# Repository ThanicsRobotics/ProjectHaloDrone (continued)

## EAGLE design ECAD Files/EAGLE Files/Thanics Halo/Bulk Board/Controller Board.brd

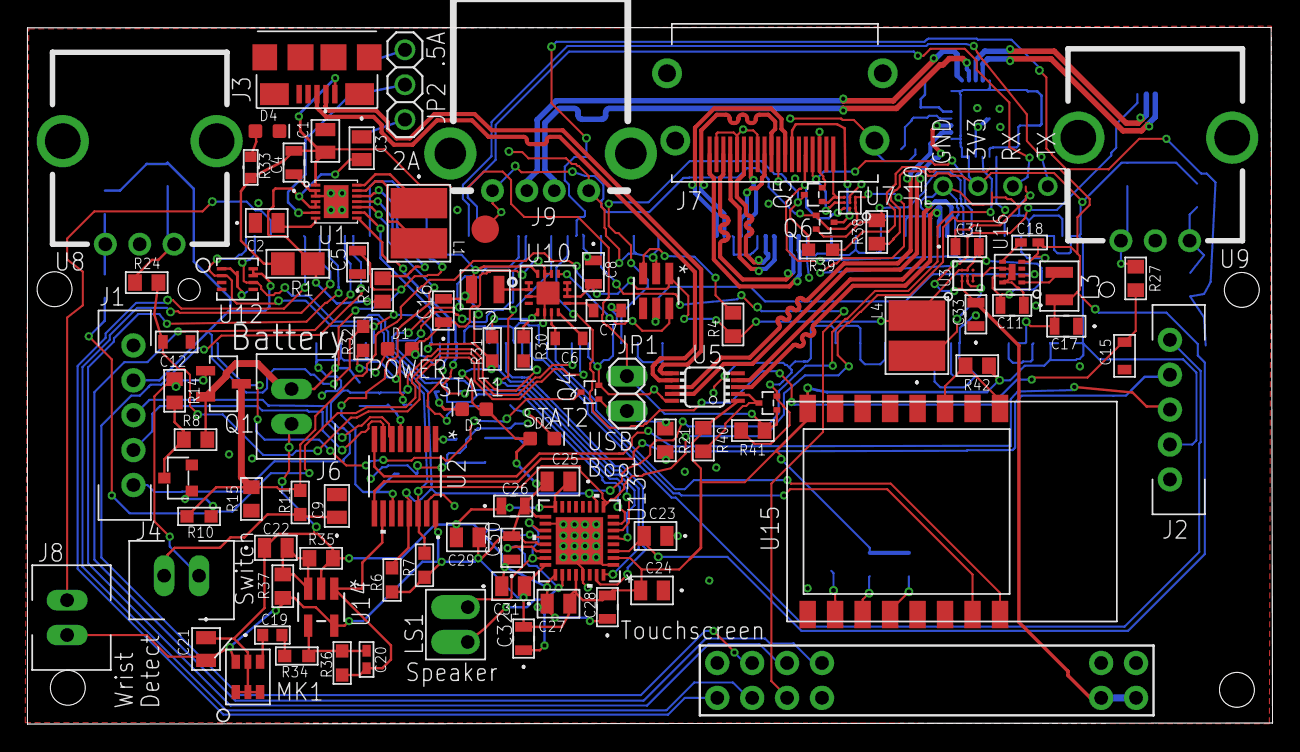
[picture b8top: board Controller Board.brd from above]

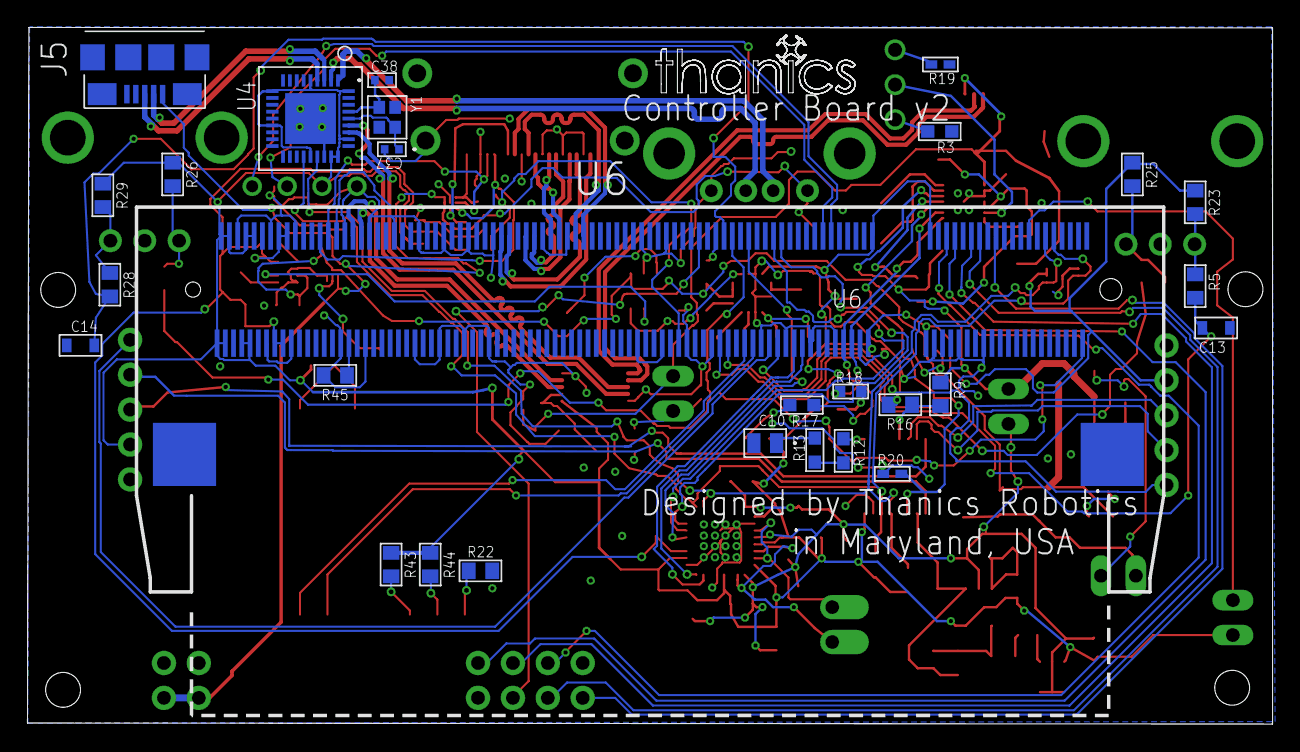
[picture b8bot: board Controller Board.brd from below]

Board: 2 copper layers, 90.6 x 50.7 mm, 129 parts (28 on the bottom side), 115 nets.

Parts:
C1, C2, C10, C21, C23, C24, C25, C27, C29, C31: 0.1uF; 0805
C3, C9, C22: 1uF; YAG_CC0805
C4, C8, C11, C17, C26, C28, C33, C34: 10uF; G-21
C5, C16, C30, C32: 22uF; G-21
C6, C7, C12, C13, C14, C15: 10nF; 0603_CAPACITOR
C18, C20: 560pF; CC0402N-M
C19: 2.2uF; G-188-M
C37, C38: 16pF; G-155-M
D1, D2, D4: GREEN; LED-0603
D3: RED; LED-0603
J1, J2: JOYSTICK; JST-XH_5POS
J3, J5: USB_MICRO_B_SMT
J4, J8: 2_PIN_CONNECTOR; XH_CONNECTOR
J6: POWER_CONNECTOR; XH_CONNECTOR
J7: HDMI
J9: USB_A_RECEPT
J10: 4_PIN_TELE_CONNECTOR
JP1: 1X02
JP2: 1X03
L1, L4: 4.7uH; IND_IFSC_1515AH-M
L2, L3: 470nH; 470NH_INDUCTOR
LS1: SPEAKER
MK1: SISONIC_MICROPHONE
Q1: DMP3030SN_MOSFET; SC59_MOSFET
Q2: SOT-23_(TO-236AB)
Q3, Q4, Q5, Q6: SOT-523
R1: 100; 1206
R2, R4, R5, R8, R9, R14, R15, R16, R21, R22, R23, R24, R25, R26, R27, R28, R29, R35, R37, R40, R41, R42, R43, R44, R45: 10k; RC0805N
R3, R10, R36, R39: 100k; RC0603N-M
R6, R7, R12, R13, R34: 1k; RC0603N-M
R11: 1M; RC0603N-M
R17, R32: 20R; RC0603N-M
R18, R33: 340R; RC0603N
R19, R20: 24.9k; RC0402N-M
R30: 160k; RC0603N-M
R31: 499k; RC0603N-M
R38: NF; RC0805N
TP1: TPSQTP20R; TP20R
U1: AAT3620_BATT_CHARGER; AAT3620_TDFN
U2: 8 CH; 21-0055H_16-M
U3: YFF9
U4: 36-SQFN
U5: FSUSB42MSOP10; MSOP10
U6: COMPUTE_MODULE; SO-DIMM
U7: ESD5384; WLCSP9
U8, U9: PEC12R
U10: TPS6209; VQFN16
U11: LM3880MF-1AA/NOPBMF06A-M; MF06A-M
U12: APPLE_2.0C_COPROCESSOR; PG-USON-8-1
U13: RHB32_3P45X3P45
U14: SOT-23-5_MC-M
U15: ESP-12
U16: MIC23050; MLF(ML)_8PIN
U$12: 3.5_TOUCHSCREEN
U$25: AGND-DGND
Y1: 24MHZ; FA-128

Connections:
+1V8: C17.2, C18.2, C23.2, L3.P$2, R39.1, U6.183, U6.184, U6.185, U6.186, U13.3, U16.4
+3V3: C16.2, C21.2, C24.2, C25.2, C26.2, C27.2, C28.2, C29.2, C30.2, C31.2, C32.2, D2.A, D3.A, J1.2, J2.2, J8.2, J10.3, L2.P$2, MK1.6, R6.1, R7.1, R23.1, R25.1, R26.1, R29.1, R31.1, R32.2, R37.1, R38.1, R40.1, R42.1, R43.1, R44.1, U2.16, U4.5, U4.10, U4.15, U4.23, U4.26, U4.27, U4.29, U4.36, U5.1, U6.39, U6.40, U6.41, U6.42, U6.191, U6.192, U6.193, U6.194, U6.197, U6.198, U6.199, U6.200, U10.16, U12.7, U12.8, U13.2, U13.17, U13.21, U13.24, U13.28, U14.5, U15.8
+5V: C33.2, J5.1, J9.1, Q6.G, TP1.TP, U3.A1, U3.A2, U7.A1, U7.B1, U7.C1, U$12.1, U$12.2
AGND: C21.1, C22.1, C25.1, C26.1, C27.1, C28.1, C29.1, C30.1, C31.1, C32.1, MK1.1, MK1.2, MK1.3, MK1.5, R35.2, U13.16, U13.20, U13.25, U14.2, U$25.1
D1_N: J3.2, U5.6
D1_P: J3.3, U5.7
D2_N: U4.30, U5.8
D2_P: U4.31, U5.9
DS1_N: J9.2, U4.1
DS1_P: J9.3, U4.2
DS2_N: J5.2, U4.3
DS2_P: J5.3, U4.4
EMMC_DISABLE_N: Q4.D, U6.2
ENCODER1_A: C13.2, R5.2, U6.76
ENCODER1_B: C12.2, R24.2, U6.78
ENCODER2_A: C15.2, R27.2, U6.75
ENCODER2_B: C14.2, R28.2, U6.77
GND: C1.1, C2.1, C3.1, C4.1, C5.1, C7.1, C8.1, C9.2, C10.2, C11.1, C12.1, C13.1, C14.1, C15.1, C16.1, C17.1, C23.1, C24.1, C33.1, C34.1, C37.2, C38.2, D1.C, D4.C, J1.1, J2.1, J3.4, J3.5, J3.6, J3.7, J3.P$1, J3.P$2, J3.P$3, J3.P$4, J5.4, J5.5, J5.6, J5.7, J5.P$1, J5.P$2, J5.P$3, J5.P$4, J6.2, J7.2, J7.5, J7.8, J7.11, J7.17, J7.P$1, J7.P$2, J7.P$3, J7.P$4, J9.4, J9.5, J9.6, J10.4, Q2.S, Q3.S, Q4.S, Q5.S, R3.1, R15.1, R16.2, R19.1, R20.1, R21.2, R22.2, R30.2, R41.2, R45.2, U1.2, U1.3, U1.EP, U2.15, U3.C1, U3.C2, U4.25, U4.EP, U5.5, U5.10, U6.1, U6.7, U6.8, U6.13, U6.14, U6.19, U6.20, U6.25, U6.26, U6.31, U6.32, U6.37, U6.38, U6.43, U6.44, U6.49, U6.50, U6.55, U6.56, U6.61, U6.62, U6.67, U6.68, U6.73, U6.74, U6.79, U6.80, U6.85, U6.86, U6.91, U6.92, U6.97, U6.98, U6.103, U6.104, U6.109, U6.110, U6.115, U6.116, U6.121, U6.122, U6.127, U6.133, U6.134, U6.139, U6.140, U6.145, U6.146, U6.151, U6.152, U6.157, U6.163, U6.164, U6.169, U6.170, U6.181, U6.182, U6.187, U6.188, U6.195, U6.196, U6.G1, U6.G2, U7.B2, U7.C2, U8.C, U9.C, U10.3, U10.6, U10.14, U10.15, U10.17, U11.2, U12.1, U12.9, U13.1, U13.18, U13.29, U13.33, U15.9, U16.6, U16.8, U16.EP, U$12.3, U$12.7, U$25.2
GPIO18: U6.63, U13.7
GPIO19: U6.65, U13.6
GPIO21: U6.71, U13.5
GPIO25: U6.83, U$12.4
GPIO36: U6.58, U13.32
GPIO37: U6.60, U13.31
HDMI_CEC: Q6.S, R38.2, U6.171
HDMI_CK_N: J7.12, U6.111
HDMI_CK_P: J7.10, U6.113
HDMI_D0_N: J7.9, U6.117
HDMI_D0_P: J7.7, U6.119
HDMI_D1_N: J7.6, U6.123
HDMI_D1_P: J7.4, U6.125
HDMI_D2_N: J7.3, U6.129
HDMI_D2_P: J7.1, U6.131
HDMI_HPD_N_1V8: Q5.D, R39.2, U6.88
HDMI_SCL: J7.15, U6.175, U7.A3
HDMI_SDA: J7.16, U6.173, U7.B3
I2C_SCL: R6.2, U2.13, U4.24, U6.11, U12.6, U13.10
I2C_SDA: R7.2, U2.14, U4.22, U6.9, U12.2, U13.9
ISET: JP2.2, U1.6
ITERM: R20.2, U1.10, U2.11
J1_SW: J1.5, U6.64
J2_SW: J2.5, U6.66
MIC_OUTPUT: C20.2, R36.1, U2.10, U14.1
unnamed: J4.1, Q1.G, R14.1
unnamed: C2.2, U1.7
unnamed: JP1.2, Q4.G, R21.1
unnamed: L1.2, U1.13
unnamed: L1.1, U1.14
unnamed: C3.2, R1.1, R2.1, U1.4, U1.5
unnamed: C5.2, J6.1, Q1.S, R8.2, R9.1, U1.12
unnamed: U10.13, U11.6
unnamed: D4.A, R33.1
unnamed: D1.A, R32.1
unnamed: R2.2, U1.11
unnamed: U11.5, U16.2
unnamed: C6.2, U10.7
unnamed: C19.1, MK1.4
unnamed: D2.C, R17.2
unnamed: R12.1, U2.1
unnamed: J1.3, U2.6
unnamed: J1.4, U2.7
unnamed: J2.3, U2.8
unnamed: J2.4, U2.9
unnamed: C19.2, R34.2
unnamed: D3.C, R18.2
unnamed: C6.1, U10.8
unnamed: R12.2, R13.1
unnamed: Q2.G, R10.1
unnamed: C9.1, J4.2, R11.1
unnamed: Q2.D, R8.1, R14.2
unnamed: C10.1, R13.2
unnamed: C7.2, U10.9
unnamed: L2.P$1, U10.1, U10.2
unnamed: R5.1, R23.2, U8.A
unnamed: L3.P$1, U16.1
unnamed: R42.2, U15.1, U15.3
unnamed: R24.1, R25.2, U8.B
unnamed: C20.1, R34.1, R36.2, U14.4
unnamed: C22.2, R35.1, R37.2, U14.3
unnamed: R26.2, R27.1, U9.A
unnamed: R28.1, R29.2, U9.B
unnamed: R9.2, R16.1, U2.5
unnamed: JP2.1, R3.2
unnamed: LS1.1, U13.22, U13.26
unnamed: JP2.3, R19.2
unnamed: R22.1, U15.10
unnamed: LS1.2, U13.19, U13.23
unnamed: R43.2, U15.12
unnamed: R30.1, R31.2, U10.5
unnamed: C8.2, C11.2, C34.2, L4.2, Q1.D, R4.1, R10.2, R11.2, R15.2, U3.A3, U3.B3, U10.10, U10.11, U10.12, U11.1, U16.7
unnamed: C18.1, U16.5
unnamed: J7.13, Q6.D, U7.A2
unnamed: J7.19, Q5.G, U7.C3
unnamed: R44.2, U15.11
unnamed: C38.1, U4.33, Y1.1
unnamed: R45.1, U6.168
unnamed: J8.1, U6.15
unnamed: Q3.D, R40.2, U5.2
unnamed: C37.1, U4.32, Y1.3
unnamed: L4.1, U3.B1, U3.B2
POWER_SEQ_EN: R4.2, U11.3
SPI_CS0: U6.27, U$12.5
SPI_CS1: U6.23, U$12.6
SPI_MISO: U6.29, U$12.9
SPI_MOSI: U6.33, U$12.10
SPI_SCLK: U6.35, U$12.8
STAT1: R17.1, U1.9, U6.46
STAT2: R18.1, U1.8, U6.48
UART2_RX: U6.72, U15.16
UART2_TX: U6.70, U15.15
UART_RX: J10.2, U6.53
UART_TX: J10.1, U6.51
USB_5V: C1.2, C4.2, J3.1, JP1.1, Q3.G, R1.2, R33.2, R41.1, U1.1
USB_D_N: U5.4, U6.167
USB_D_P: U5.3, U6.165
